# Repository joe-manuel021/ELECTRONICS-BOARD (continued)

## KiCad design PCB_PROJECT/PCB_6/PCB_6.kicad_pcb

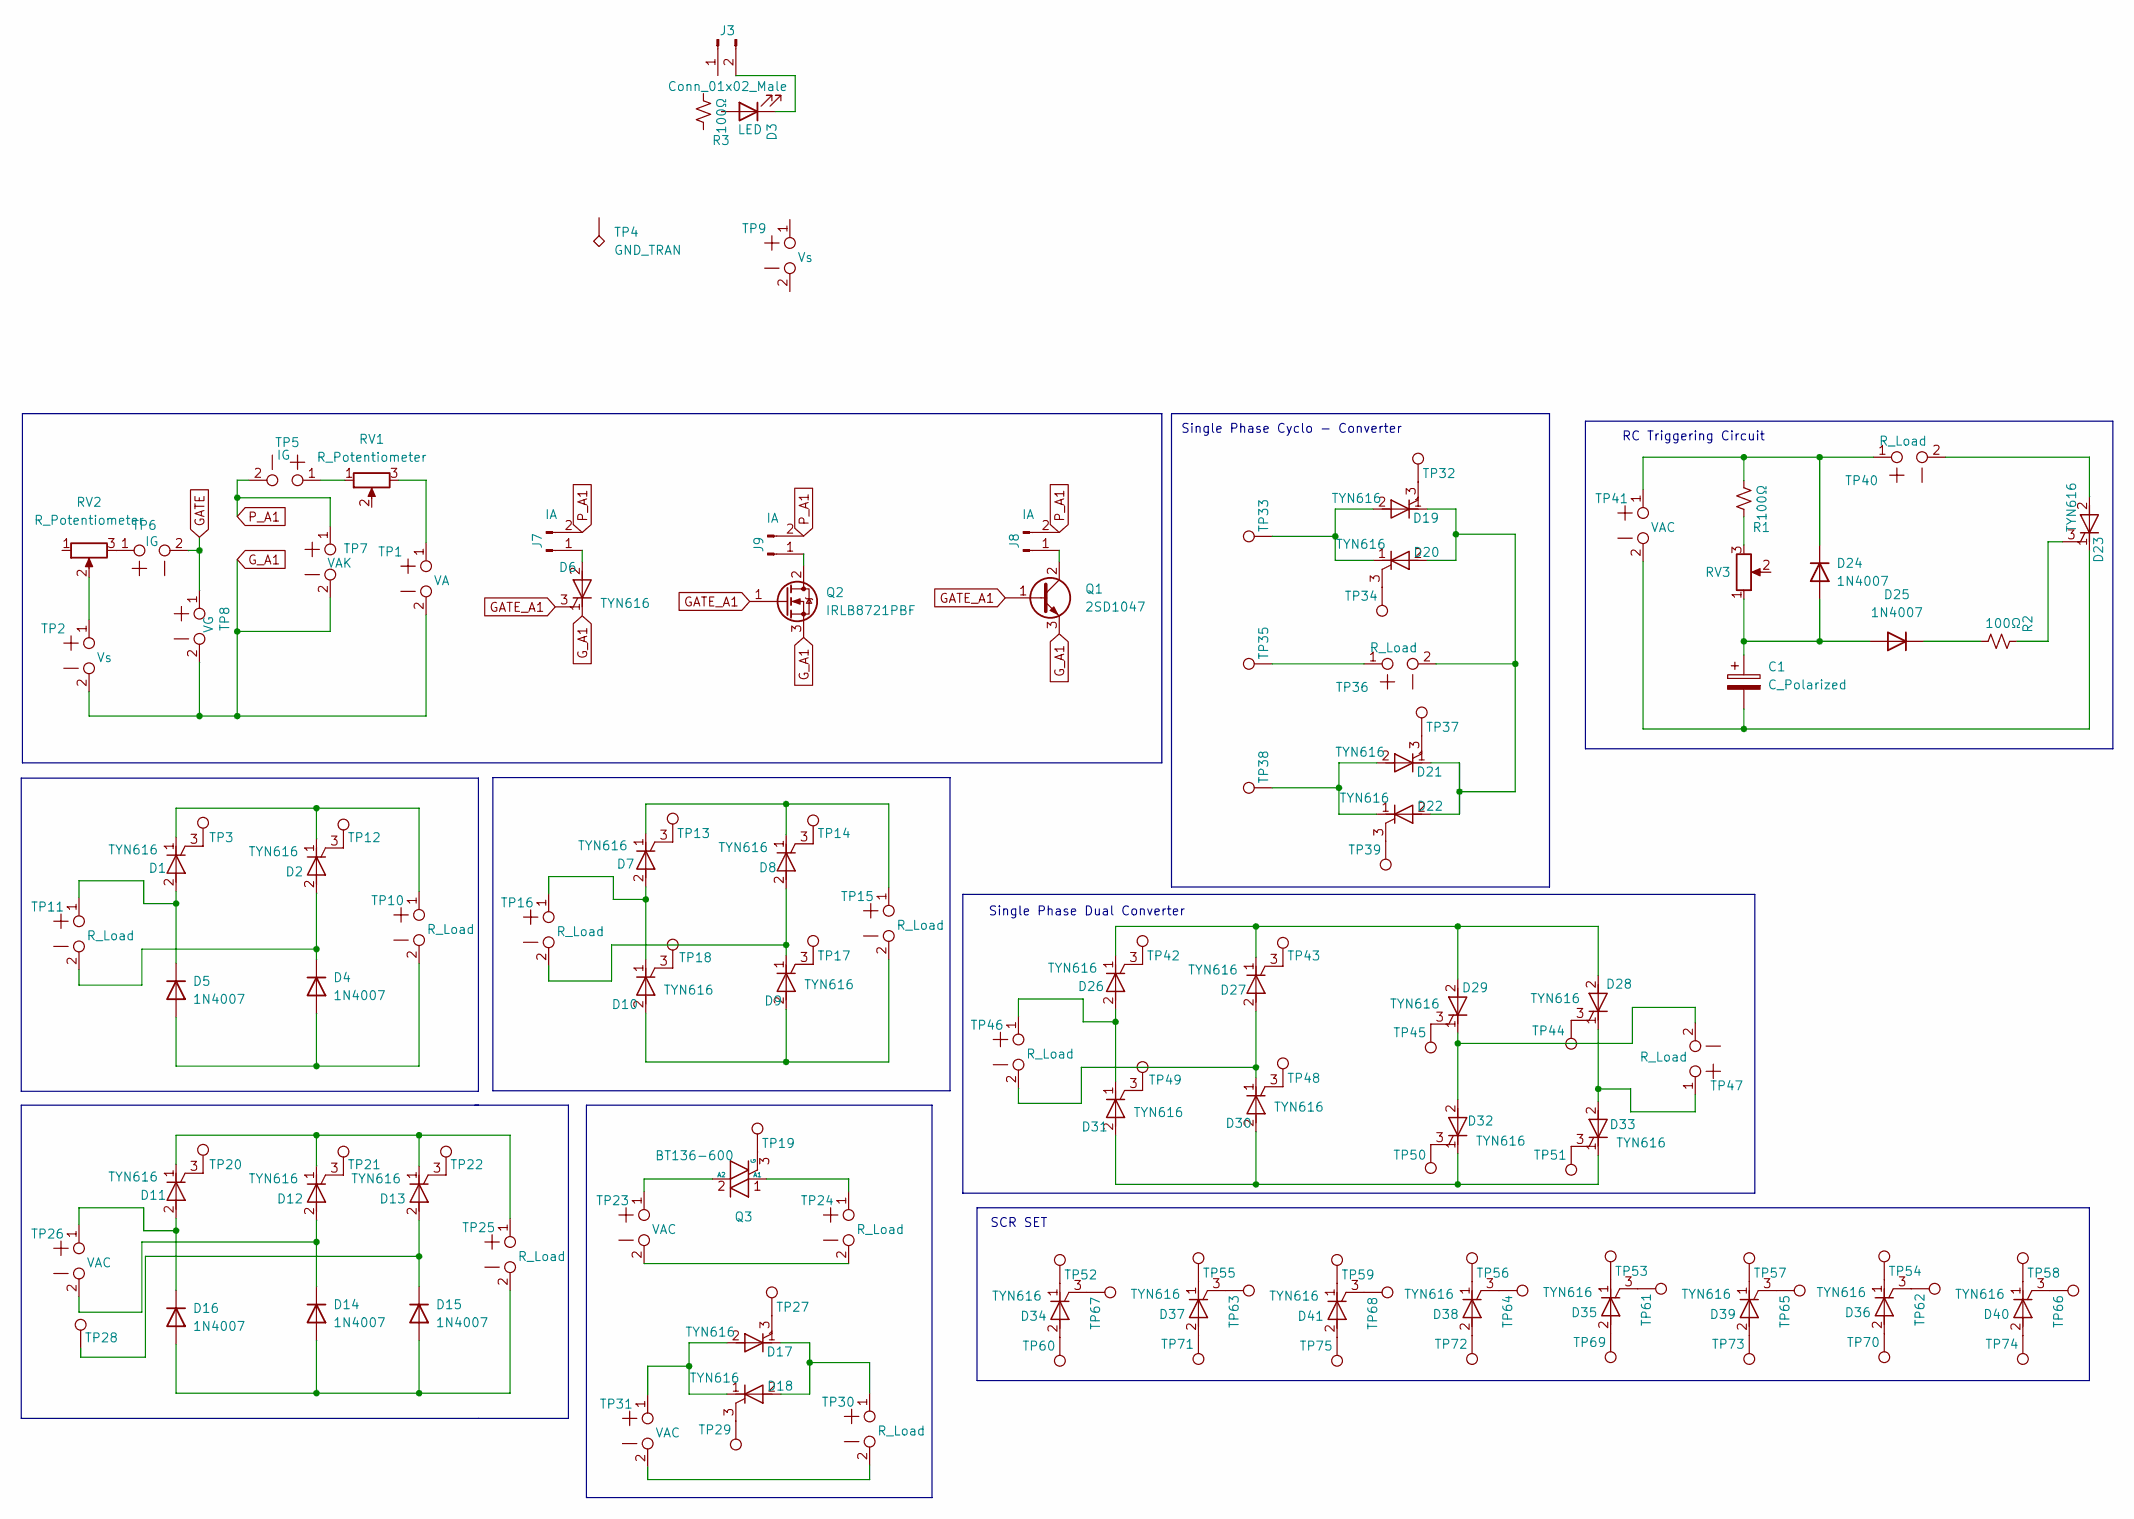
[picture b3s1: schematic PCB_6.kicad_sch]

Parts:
C1: C_Polarized
D1, D2, D6, D7, D8, D9, D10, D11, D12, D13, D17, D18, D19, D20, D21, D22, D23, D26, D27, D28, D29, D30, D31, D32, D33, D34, D35, D36, D37, D38, D39, D40, D41: TYN616; TO-220-3_Vertical
D3: LED; LED_D3.0mm
D4, D5, D14, D15, D16, D24, D25: 1N4007; D_DO-41_SOD81_P10.16mm_Horizontal
J3: Conn_01x02_Male; PinHeader_1x02_P2.54mm_Vertical
J7, J8, J9: IA; PinHeader_1x02_P2.54mm_Vertical
Q1: 2SD1047; TO-3PB-3_Vertical
Q2: IRLB8721PBF; TO-220-3_Vertical
Q3: BT136-600; TO-220-3_Vertical
R1, R2, R3: 100Ω; R_0805_2012Metric_Pad1.20x1.40mm_HandSolder
RV1, RV2, RV3: R_Potentiometer; Potentiometer_Piher_T-16L_Single_Vertical_Hole
TP1: VA; TestPoint_Pith10mm_Drill4mm
TP2, TP9: Vs; TestPoint_Pith10mm_Drill4mm
TP3, TP12, TP13, TP14, TP17, TP18, TP19, TP20, TP21, TP22, TP27, TP28, TP29, TP32, TP33, TP34, TP35, TP37, TP38, TP39, TP42, TP43, TP44, TP45, TP48, TP49, TP50, TP51, TP60, TP69, TP70, TP71, TP72, TP73, TP74, TP75: POWER_4MM
TP4: GND_TRAN; GND_4MM
TP5, TP6: IG; TestPoint_Pith10mm_Drill4mm
TP7: VAK; TestPoint_Pith10mm_Drill4mm
TP8: VG; TestPoint_Pith10mm_Drill4mm
TP10, TP11, TP15, TP16, TP24, TP25, TP30, TP36, TP40, TP46, TP47: R_Load; TestPoint_Pith10mm_Drill4mm
TP23, TP26, TP31, TP41: VAC; TestPoint_Pith10mm_Drill4mm
TP52, TP53, TP54, TP55, TP56, TP57, TP58, TP59: GND_4MM
TP61, TP62, TP63, TP64, TP65, TP66, TP67, TP68: POWER_4MM_GREEN

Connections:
GATE: TP6.2, TP8.1
GATE_A1: D6.3 (G), Q1.1 (B), Q2.1 (G)
G_A1: D6.1 (K), Q1.3 (E), Q2.3 (S), TP1.2, TP2.2, TP7.2, TP8.2
unnamed: C1.1, D24.2 (A), D25.2 (A), RV3.1
unnamed: C1.2, D23.1 (K), TP41.2
unnamed: D1.1 (K), D2.1 (K), TP10.1
unnamed: D1.2 (A), D5.1 (K), TP11.1
unnamed: D1.3 (G), TP3.1
unnamed: D2.2 (A), D4.1 (K), TP11.2
unnamed: D2.3 (G), TP12.1
unnamed: D3.1 (K), J3.2
unnamed: D4.2 (A), D5.2 (A), TP10.2
unnamed: D6.2 (A), J7.1
unnamed: D7.1 (K), D8.1 (K), TP15.1
unnamed: D7.3 (G), TP13.1
unnamed: D8.2 (A), D9.1 (K), TP16.2
unnamed: D8.3 (G), TP14.1
unnamed: D9.3 (G), TP17.1
unnamed: D7.2 (A), D10.1 (K), TP16.1
unnamed: D9.2 (A), D10.2 (A), TP15.2
unnamed: D10.3 (G), TP18.1
unnamed: D11.1 (K), D12.1 (K), D13.1 (K), TP25.1
unnamed: D11.2 (A), D16.1 (K), TP26.1
unnamed: D11.3 (G), TP20.1
unnamed: D12.2 (A), D14.1 (K), TP26.2
unnamed: D12.3 (G), TP21.1
unnamed: D13.2 (A), D15.1 (K), TP28.1
unnamed: D13.3 (G), TP22.1
unnamed: D14.2 (A), D15.2 (A), D16.2 (A), TP25.2
unnamed: D17.1 (K), D18.2 (A), TP30.1
unnamed: D17.2 (A), D18.1 (K), TP31.1
unnamed: D17.3 (G), TP27.1
unnamed: D18.3 (G), TP29.1
unnamed: D19.1 (K), D20.2 (A), D21.1 (K), D22.2 (A), TP36.2
unnamed: D19.2 (A), D20.1 (K), TP33.1
unnamed: D19.3 (G), TP32.1
unnamed: D20.3 (G), TP34.1
unnamed: D21.2 (A), D22.1 (K), TP38.1
unnamed: D21.3 (G), TP37.1
unnamed: D22.3 (G), TP39.1
unnamed: D23.2 (A), TP40.2
unnamed: D23.3 (G), R2.2
unnamed: D24.1 (K), R1.1, TP40.1, TP41.1
unnamed: D25.1 (K), R2.1
unnamed: D26.1 (K), D27.1 (K), D28.2 (A), D29.2 (A)
unnamed: D26.2 (A), D31.1 (K), TP46.1
unnamed: D26.3 (G), TP42.1
unnamed: D27.2 (A), D30.1 (K), TP46.2
unnamed: D27.3 (G), TP43.1
unnamed: D28.1 (K), D33.2 (A), TP47.1
unnamed: D28.3 (G), TP44.1
unnamed: D29.1 (K), D32.2 (A), TP47.2
unnamed: D29.3 (G), TP45.1
unnamed: D30.2 (A), D31.2 (A), D32.1 (K), D33.1 (K)
unnamed: D30.3 (G), TP48.1
unnamed: D31.3 (G), TP49.1
unnamed: D32.3 (G), TP50.1
unnamed: D33.3 (G), TP51.1
unnamed: D34.1 (K), TP52.1
unnamed: D34.2 (A), TP60.1
unnamed: D34.3 (G), TP67.1
unnamed: D35.1 (K), TP53.1
unnamed: D35.2 (A), TP69.1
unnamed: D35.3 (G), TP61.1
unnamed: D36.1 (K), TP54.1
unnamed: D36.2 (A), TP70.1
unnamed: D36.3 (G), TP62.1
unnamed: D37.1 (K), TP55.1
unnamed: D37.2 (A), TP71.1
unnamed: D37.3 (G), TP63.1
unnamed: D38.1 (K), TP56.1
unnamed: D38.2 (A), TP72.1
unnamed: D38.3 (G), TP64.1
unnamed: D39.1 (K), TP57.1
unnamed: D39.2 (A), TP73.1
unnamed: D39.3 (G), TP65.1
unnamed: D40.1 (K), TP58.1
unnamed: D40.2 (A), TP74.1
unnamed: D40.3 (G), TP66.1
unnamed: D41.1 (K), TP59.1
unnamed: D41.2 (A), TP75.1
unnamed: D41.3 (G), TP68.1
unnamed: J8.1, Q1.2 (C)
unnamed: J9.1, Q2.2 (D)
unnamed: Q3.1 (A1), TP24.1
unnamed: Q3.2 (A2), TP23.1
unnamed: Q3.3 (G), TP19.1
unnamed: R1.2, RV3.3
unnamed: RV1.1, TP5.1
unnamed: RV1.3, TP1.1
unnamed: RV2.2, TP2.1
unnamed: RV2.3, TP6.1
unnamed: TP23.2, TP24.2
unnamed: TP30.2, TP31.2
unnamed: TP35.1, TP36.1
P_A1: J7.2, J8.2, J9.2, TP5.2, TP7.1

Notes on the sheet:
SCR SET
RC Triggering Circuit
Single Phase Dual Converter
Single Phase Cyclo - Converter

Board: 2 copper layers, 129 parts (0 on the bottom side), 96 nets, no tracks yet.

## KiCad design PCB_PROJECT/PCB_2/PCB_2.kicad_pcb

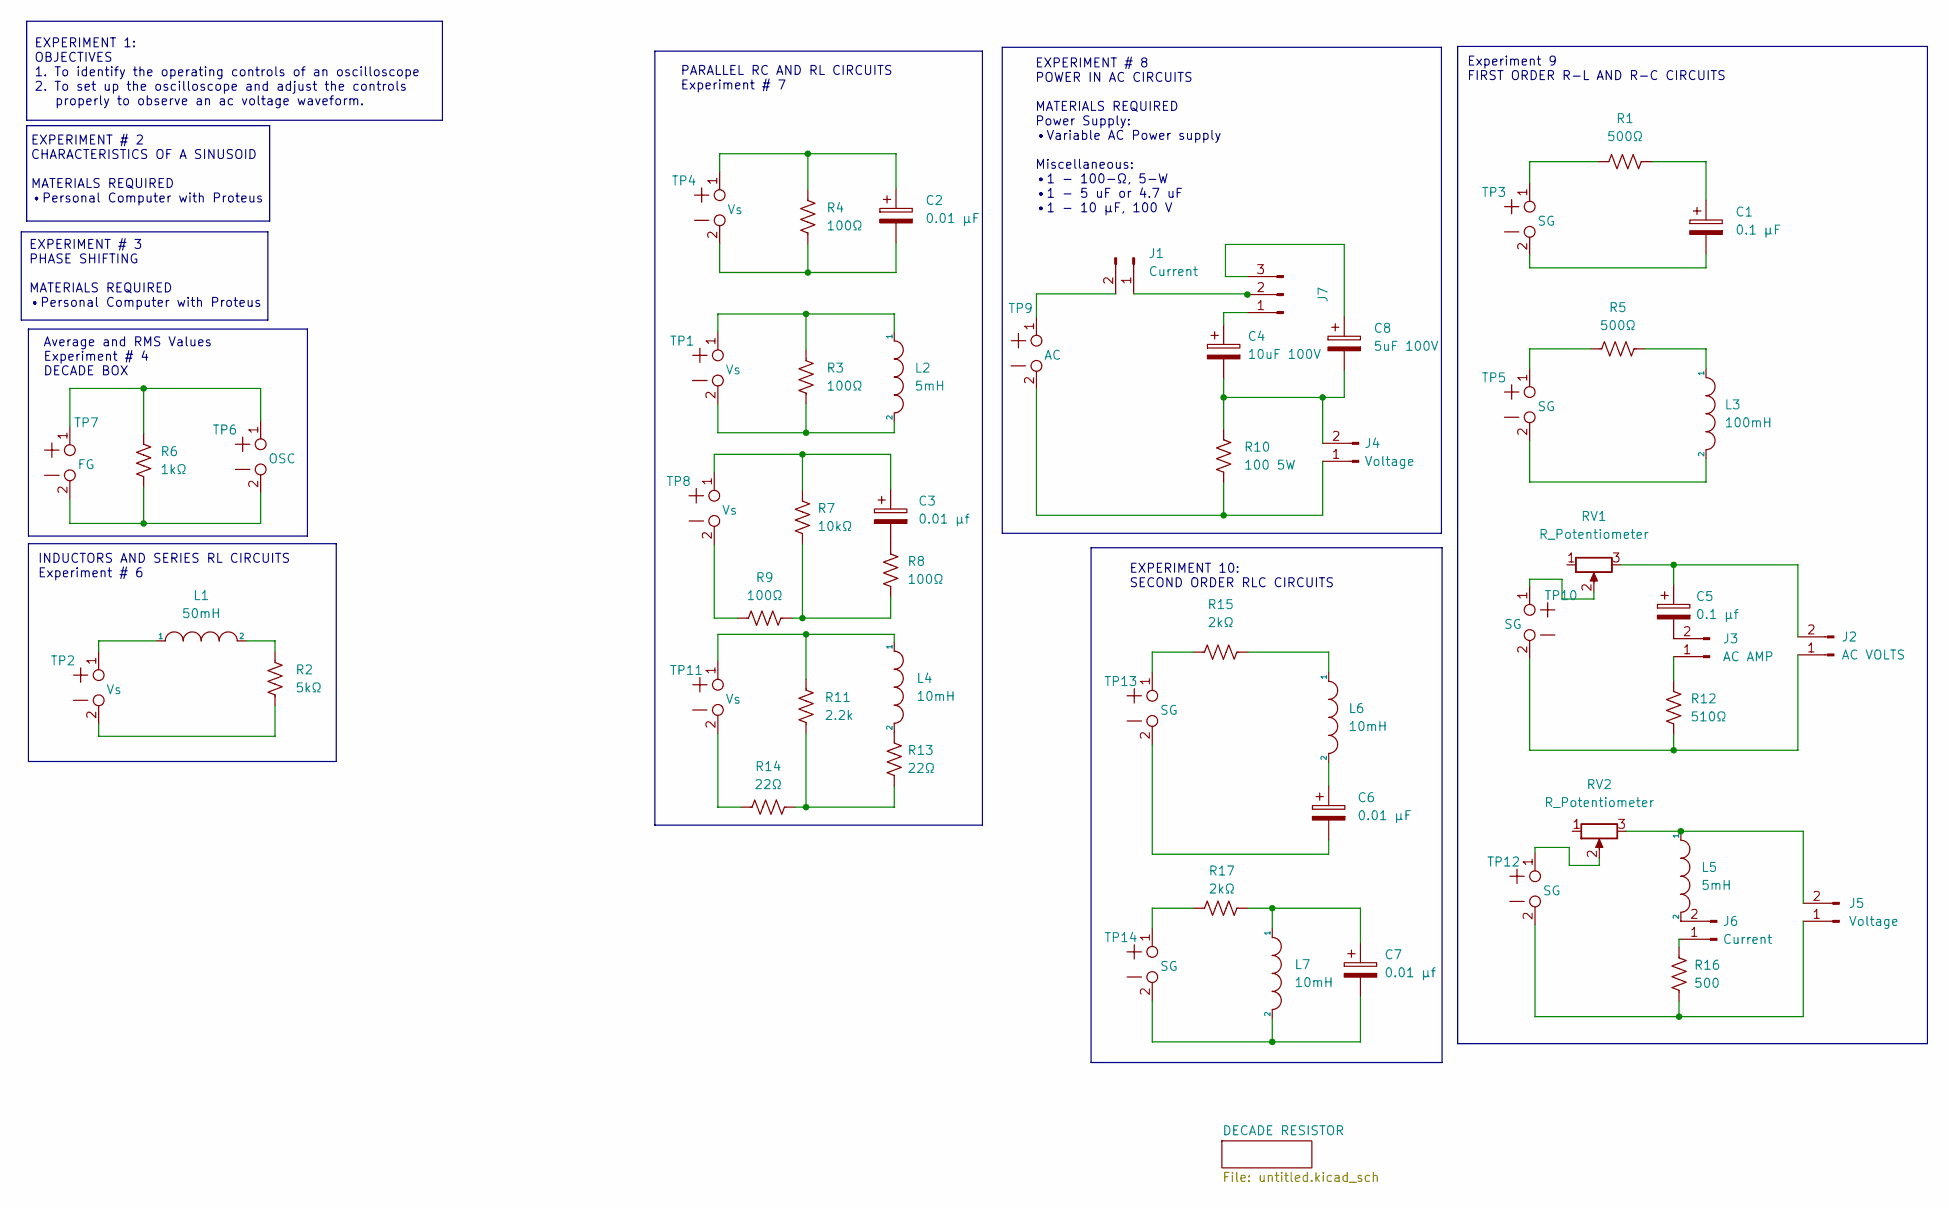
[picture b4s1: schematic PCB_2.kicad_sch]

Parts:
C1: 0.1 μF; 0.022uF_Capacitor
C2: 0.01 μF; C_Rect_L10.0mm_W4.0mm_P7.50mm_MKS4
C3: 0.01 μf; C_Rect_L10.0mm_W4.0mm_P7.50mm_MKS4
C4: 10uF 100V; CP_Elec_6.3x7.7
C5: 0.1 μf; 0.022uF_Capacitor
C6: 0.01 μF; 0.022uF_Capacitor
C7: 0.01 μf; 0.022uF_Capacitor
C8: 5uF 100V; CP_Elec_6.3x5.4
J1, J6: Current; PinHeader_1x02_P2.54mm_Vertical
J2: AC VOLTS; PinHeader_1x02_P2.54mm_Vertical
J3: AC AMP; PinHeader_1x02_P2.54mm_Vertical
J4, J5: Voltage; PinHeader_1x02_P2.54mm_Vertical
J7: Conn_01x03_Male; PinHeader_1x03_P2.54mm_Vertical
L1: 50mH; L_Axial_L12.0mm_D5.0mm_P15.24mm_Horizontal_Fastron_MISC
L2, L5: 5mH; L_Axial_L12.0mm_D5.0mm_P15.24mm_Horizontal_Fastron_MISC
L3: 100mH; L_Axial_L12.0mm_D5.0mm_P15.24mm_Horizontal_Fastron_MISC
L4, L6, L7: 10mH; L_Axial_L12.0mm_D5.0mm_P15.24mm_Horizontal_Fastron_MISC
R1, R5: 500Ω; R_Axial_DIN0309_L9.0mm_D3.2mm_P12.70mm_Horizontal
R2: 5kΩ; R_Axial_DIN0309_L9.0mm_D3.2mm_P12.70mm_Horizontal
R3, R4, R8, R9: 100Ω; R_Axial_DIN0309_L9.0mm_D3.2mm_P12.70mm_Horizontal
R6: 1kΩ; R_Axial_DIN0309_L9.0mm_D3.2mm_P12.70mm_Horizontal
R7: 10kΩ; R_Axial_DIN0309_L9.0mm_D3.2mm_P12.70mm_Horizontal
R10: 100 5W; R_Axial_DIN0922_L20.0mm_D9.0mm_P30.48mm_Horizontal
R11: 2.2k; R_Axial_DIN0309_L9.0mm_D3.2mm_P12.70mm_Horizontal
R12: 510Ω; R_Axial_DIN0309_L9.0mm_D3.2mm_P12.70mm_Horizontal
R13, R14: 22Ω; R_Axial_DIN0309_L9.0mm_D3.2mm_P12.70mm_Horizontal
R15, R17: 2kΩ; R_Axial_DIN0309_L9.0mm_D3.2mm_P12.70mm_Horizontal
R16: 500; R_Axial_DIN0309_L9.0mm_D3.2mm_P12.70mm_Horizontal
RV1, RV2: R_Potentiometer; Potentiometer_Alps_RK09Y11_Single_Horizontal
TP1, TP2, TP4, TP8, TP11: Vs; TestPoint_Pith10mm_Drill4mm
TP3, TP5, TP10, TP12, TP13, TP14: SG; TestPoint_Pith10mm_Drill4mm
TP6: OSC; TestPoint_Pith10mm_Drill4mm
TP7: FG; TestPoint_Pith10mm_Drill4mm
TP9: AC; TestPoint_Pith10mm_Drill4mm

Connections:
unnamed: C1.1, R1.2
unnamed: C1.2, TP3.2
unnamed: C2.1, R4.1, TP4.1
unnamed: C2.2, R4.2, TP4.2
unnamed: C3.1, R7.1, TP8.1
unnamed: C3.2, R8.1
unnamed: C4.1, J7.1
unnamed: C4.2, C8.2, J4.2, R10.1
unnamed: C5.1, J2.2, RV1.3
unnamed: C5.2, J3.2
unnamed: C6.1, L6.2
unnamed: C6.2, TP13.2
unnamed: C7.1, L7.1, R17.1
unnamed: C7.2, L7.2, TP14.2
unnamed: C8.1, J7.3
unnamed: J1.1, J7.2
unnamed: J1.2, TP9.1
unnamed: J2.1, R12.1, TP10.2
unnamed: J3.1, R12.2
unnamed: J4.1, R10.2, TP9.2
unnamed: J5.1, R16.1, TP12.2
unnamed: J5.2, L5.1, RV2.3
unnamed: J6.1, R16.2
unnamed: J6.2, L5.2
unnamed: L1.1, TP2.1
unnamed: L1.2, R2.1
unnamed: L2.1, R3.1, TP1.1
unnamed: L2.2, R3.2, TP1.2
unnamed: L3.1, R5.2
unnamed: L3.2, TP5.2
unnamed: L4.1, R11.1, TP11.1
unnamed: L4.2, R13.1
unnamed: L6.1, R15.1
unnamed: R1.1, TP3.1
unnamed: R2.2, TP2.2
unnamed: R5.1, TP5.1
unnamed: R6.1, TP6.1, TP7.1
unnamed: R6.2, TP6.2, TP7.2
unnamed: R7.2, R8.2, R9.2
unnamed: R9.1, TP8.2
unnamed: R11.2, R13.2, R14.2
unnamed: R14.1, TP11.2
unnamed: R15.2, TP13.1
unnamed: R17.2, TP14.1
unnamed: RV2.2, TP12.1
unnamed: RV1.2, TP10.1

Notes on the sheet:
EXPERIMENT 10: SECOND ORDER RLC CIRCUITS
INDUCTORS AND SERIES RL CIRCUITS Experiment # 6
EXPERIMENT # 2 CHARACTERISTICS OF A SINUSOID MATERIALS REQUIRED •Personal Computer with Proteus
EXPERIMENT # 3 PHASE SHIFTING MATERIALS REQUIRED •Personal Computer with Proteus
EXPERIMENT # 8 POWER IN AC CIRCUITS MATERIALS REQUIRED Power Supply: •Variable AC Power supply Miscellaneous: •1 - 100-Ω, 5-W •1 - 5 uF or 4.7 uF •1 - 10 μF, 100 V
Average and RMS Values Experiment # 4 DECADE BOX
Experiment 9 FIRST ORDER R-L AND R-C CIRCUITS
EXPERIMENT 1: OBJECTIVES 1. To identify the operating controls of an oscilloscope 2. To set up the oscilloscope and adjust the controls properly to observe an ac voltage waveform.
PARALLEL RC AND RL CIRCUITS Experiment # 7

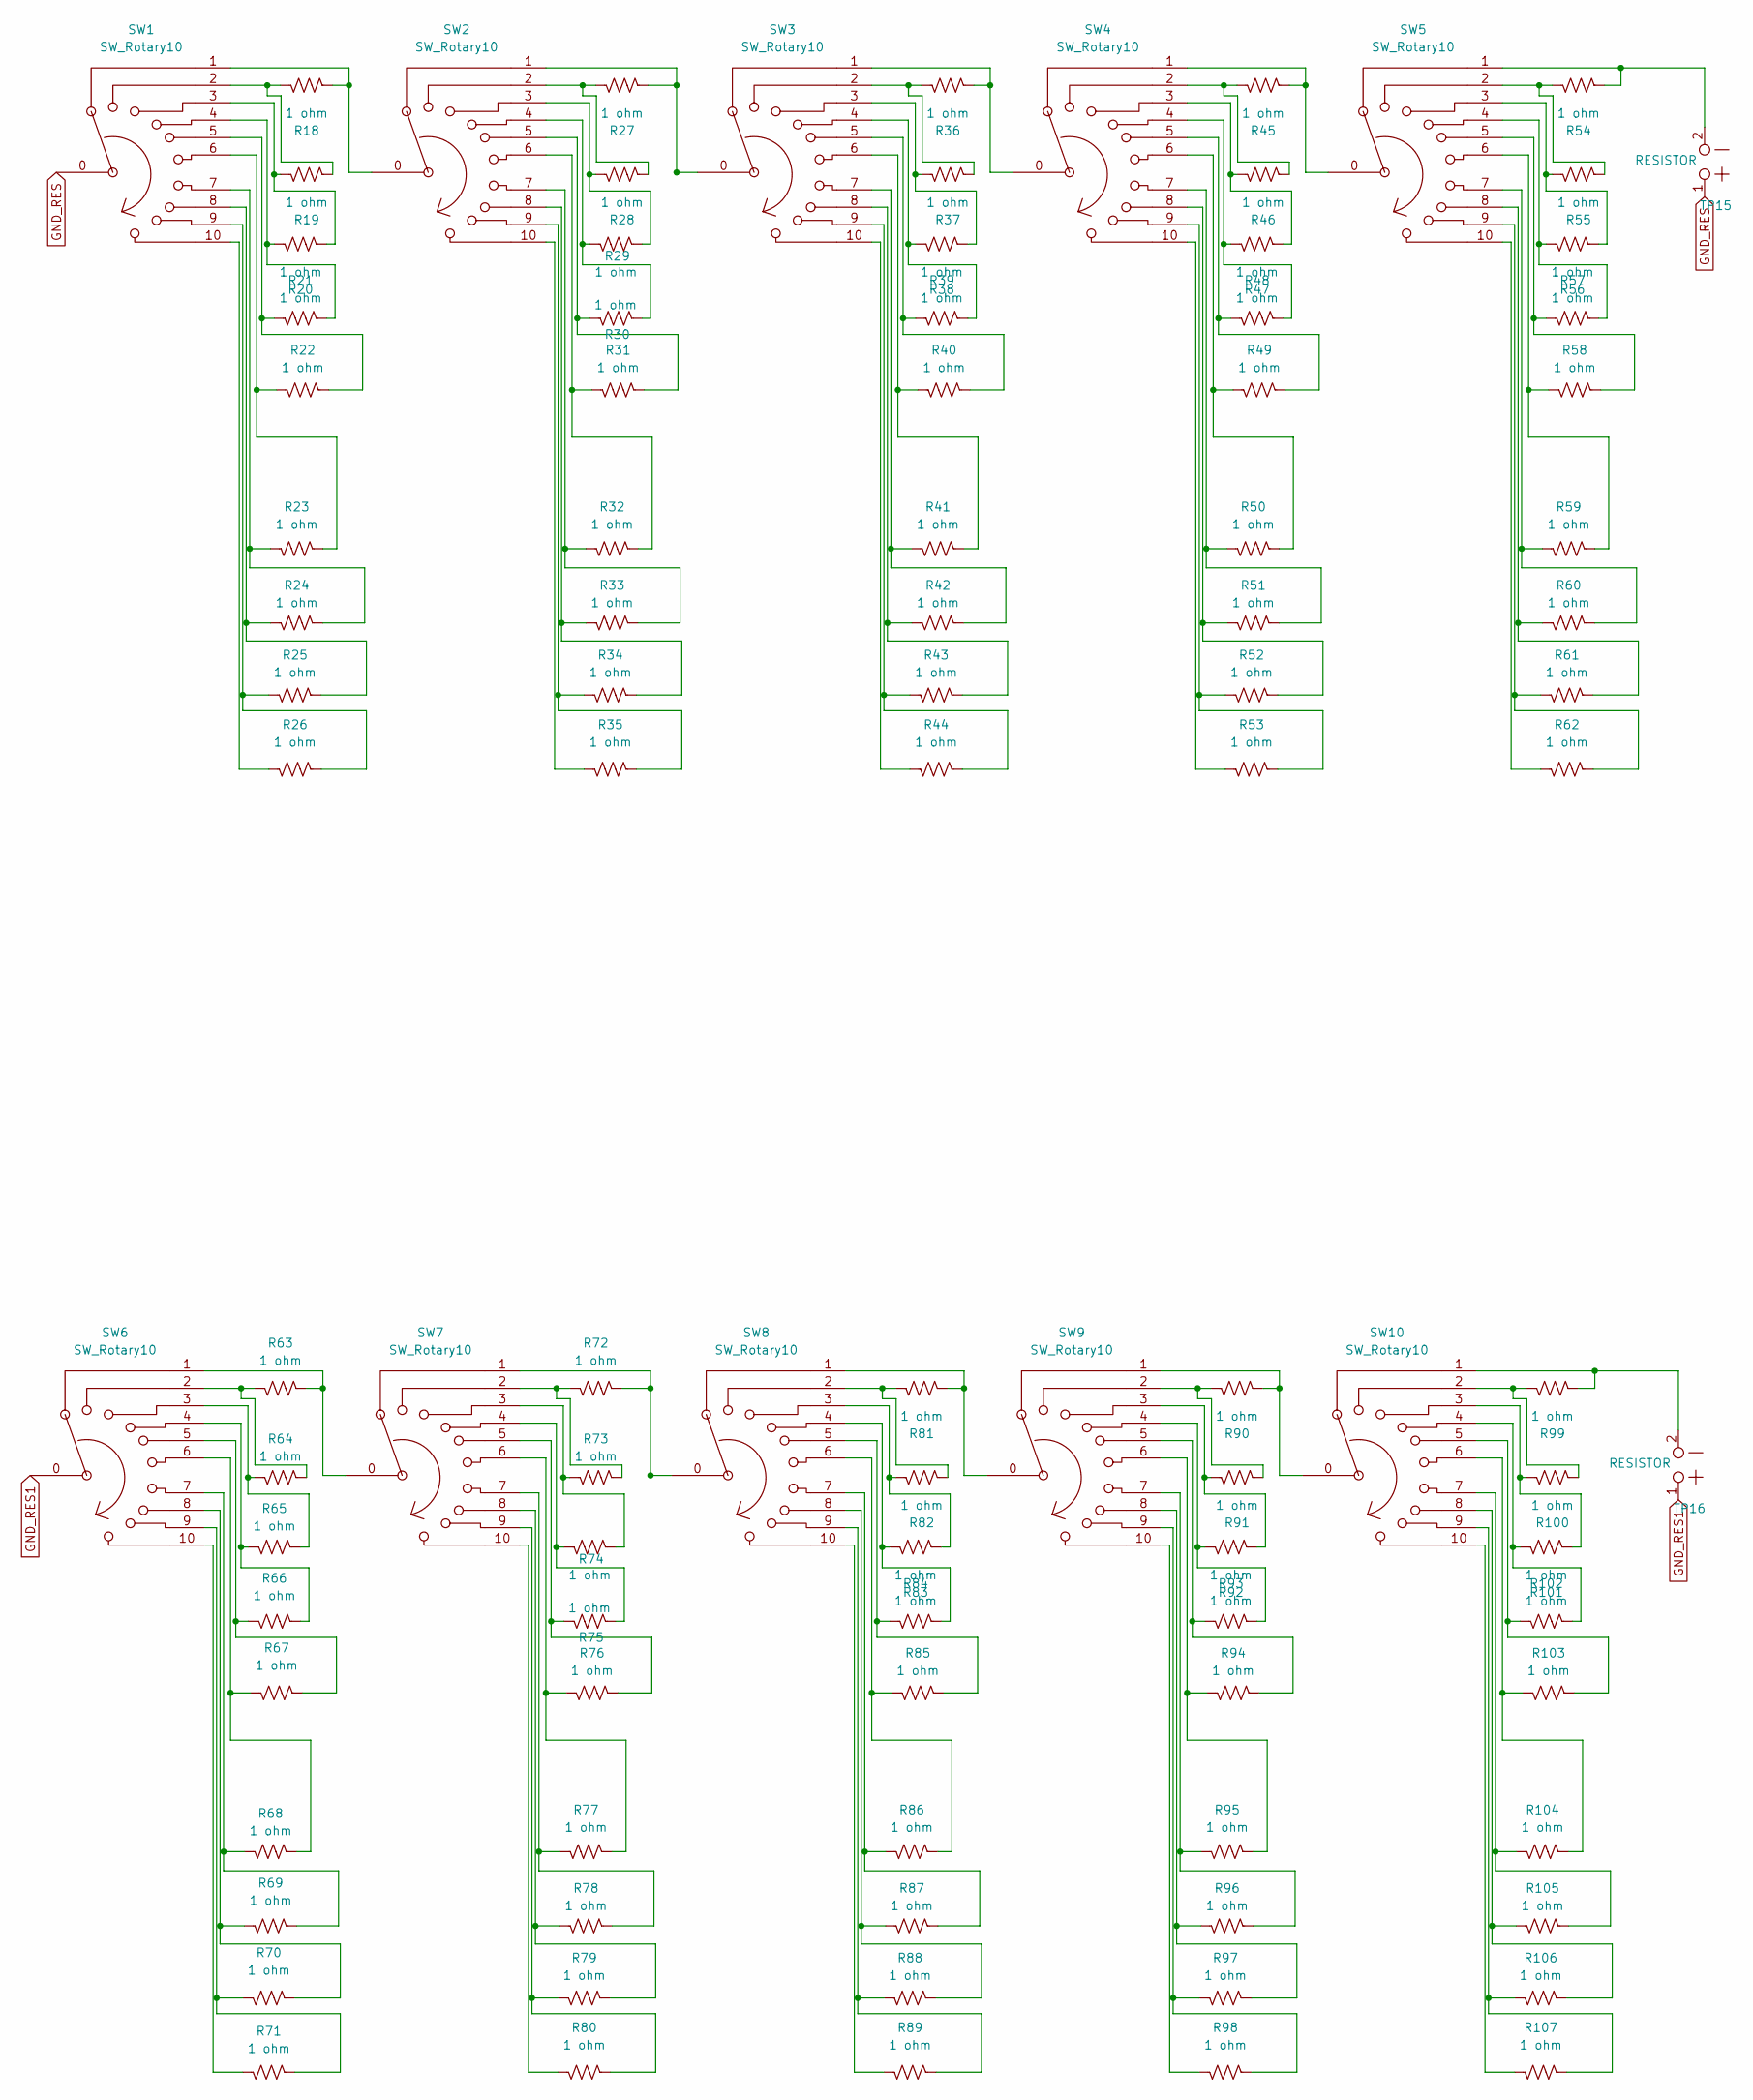
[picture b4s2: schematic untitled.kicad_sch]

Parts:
R18, R19, R20, R21, R22, R23, R24, R25, R26, R27, R28, R29, R30, R31, R32, R33, R34, R35, R36, R37, R38, R39, R40, R41, R42, R43, R44, R45, R46, R47, R48, R49, R50, R51, R52, R53, R54, R55, R56, R57, R58, R59, R60, R61, R62, R63, R64, R65, R66, R67, R68, R69, R70, R71, R72, R73, R74, R75, R76, R77, R78, R79, R80, R81, R82, R83, R84, R85, R86, R87, R88, R89, R90, R91, R92, R93, R94, R95, R96, R97, R98, R99, R100, R101, R102, R103, R104, R105, R106, R107: 1 ohm; R_Axial_DIN0207_L6.3mm_D2.5mm_P10.16mm_Horizontal
SW1, SW2, SW3, SW4, SW5, SW6, SW7, SW8, SW9, SW10: SW_Rotary10; rotary_10
TP15, TP16: RESISTOR; TestPoint_Pith10mm_Drill4mm

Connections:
GND_RES: SW1.0, TP15.1
GND_RES1: SW6.0, TP16.1
unnamed: R18.1, R19.2, SW1.2
unnamed: R18.2, SW1.1, SW2.0
unnamed: R19.1, R20.2, SW1.3
unnamed: R20.1, R21.2, SW1.4
unnamed: R21.1, R22.2, SW1.5
unnamed: R22.1, R23.2, SW1.6
unnamed: R23.1, R24.2, SW1.7
unnamed: R24.1, R25.2, SW1.8
unnamed: R25.1, R26.2, SW1.9
unnamed: R26.1, SW1.10
unnamed: R27.1, R28.2, SW2.2
unnamed: R27.2, SW2.1, SW3.0
unnamed: R28.1, R29.2, SW2.3
unnamed: R29.1, R30.2, SW2.4
unnamed: R30.1, R31.2, SW2.5
unnamed: R31.1, R32.2, SW2.6
unnamed: R32.1, R33.2, SW2.7
unnamed: R33.1, R34.2, SW2.8
unnamed: R34.1, R35.2, SW2.9
unnamed: R35.1, SW2.10
unnamed: R36.1, R37.2, SW3.2
unnamed: R36.2, SW3.1, SW4.0
unnamed: R37.1, R38.2, SW3.3
unnamed: R38.1, R39.2, SW3.4
unnamed: R39.1, R40.2, SW3.5
unnamed: R40.1, R41.2, SW3.6
unnamed: R41.1, R42.2, SW3.7
unnamed: R42.1, R43.2, SW3.8
unnamed: R43.1, R44.2, SW3.9
unnamed: R44.1, SW3.10
unnamed: R45.1, R46.2, SW4.2
unnamed: R45.2, SW4.1, SW5.0
unnamed: R46.1, R47.2, SW4.3
unnamed: R47.1, R48.2, SW4.4
unnamed: R48.1, R49.2, SW4.5
unnamed: R49.1, R50.2, SW4.6
unnamed: R50.1, R51.2, SW4.7
unnamed: R51.1, R52.2, SW4.8
unnamed: R52.1, R53.2, SW4.9
unnamed: R53.1, SW4.10
unnamed: R54.1, R55.2, SW5.2
unnamed: R54.2, SW5.1, TP15.2
unnamed: R55.1, R56.2, SW5.3
unnamed: R56.1, R57.2, SW5.4
unnamed: R57.1, R58.2, SW5.5
unnamed: R58.1, R59.2, SW5.6
unnamed: R59.1, R60.2, SW5.7
unnamed: R60.1, R61.2, SW5.8
unnamed: R61.1, R62.2, SW5.9
unnamed: R62.1, SW5.10
unnamed: R63.1, R64.2, SW6.2
unnamed: R63.2, SW6.1, SW7.0
unnamed: R64.1, R65.2, SW6.3
unnamed: R65.1, R66.2, SW6.4
unnamed: R66.1, R67.2, SW6.5
unnamed: R67.1, R68.2, SW6.6
unnamed: R68.1, R69.2, SW6.7
unnamed: R69.1, R70.2, SW6.8
unnamed: R70.1, R71.2, SW6.9
unnamed: R71.1, SW6.10
unnamed: R72.1, R73.2, SW7.2
unnamed: R72.2, SW7.1, SW8.0
unnamed: R73.1, R74.2, SW7.3
unnamed: R74.1, R75.2, SW7.4
unnamed: R75.1, R76.2, SW7.5
unnamed: R76.1, R77.2, SW7.6
unnamed: R77.1, R78.2, SW7.7
unnamed: R78.1, R79.2, SW7.8
unnamed: R79.1, R80.2, SW7.9
unnamed: R80.1, SW7.10
unnamed: R81.1, R82.2, SW8.2
unnamed: R81.2, SW8.1, SW9.0
unnamed: R82.1, R83.2, SW8.3
unnamed: R83.1, R84.2, SW8.4
unnamed: R84.1, R85.2, SW8.5
unnamed: R85.1, R86.2, SW8.6
unnamed: R86.1, R87.2, SW8.7
unnamed: R87.1, R88.2, SW8.8
unnamed: R88.1, R89.2, SW8.9
unnamed: R89.1, SW8.10
unnamed: R90.1, R91.2, SW9.2
unnamed: R90.2, SW9.1, SW10.0
unnamed: R91.1, R92.2, SW9.3
unnamed: R92.1, R93.2, SW9.4
unnamed: R93.1, R94.2, SW9.5
unnamed: R94.1, R95.2, SW9.6
unnamed: R95.1, R96.2, SW9.7
unnamed: R96.1, R97.2, SW9.8
unnamed: R97.1, R98.2, SW9.9
unnamed: R98.1, SW9.10
unnamed: R99.2, SW10.1, TP16.2
unnamed: R100.1, R101.2, SW10.3
unnamed: R99.1, R100.2, SW10.2
unnamed: R101.1, R102.2, SW10.4
unnamed: R102.1, R103.2, SW10.5
unnamed: R103.1, R104.2, SW10.6
unnamed: R104.1, R105.2, SW10.7
unnamed: R105.1, R106.2, SW10.8
unnamed: R106.1, R107.2, SW10.9
unnamed: R107.1, SW10.10

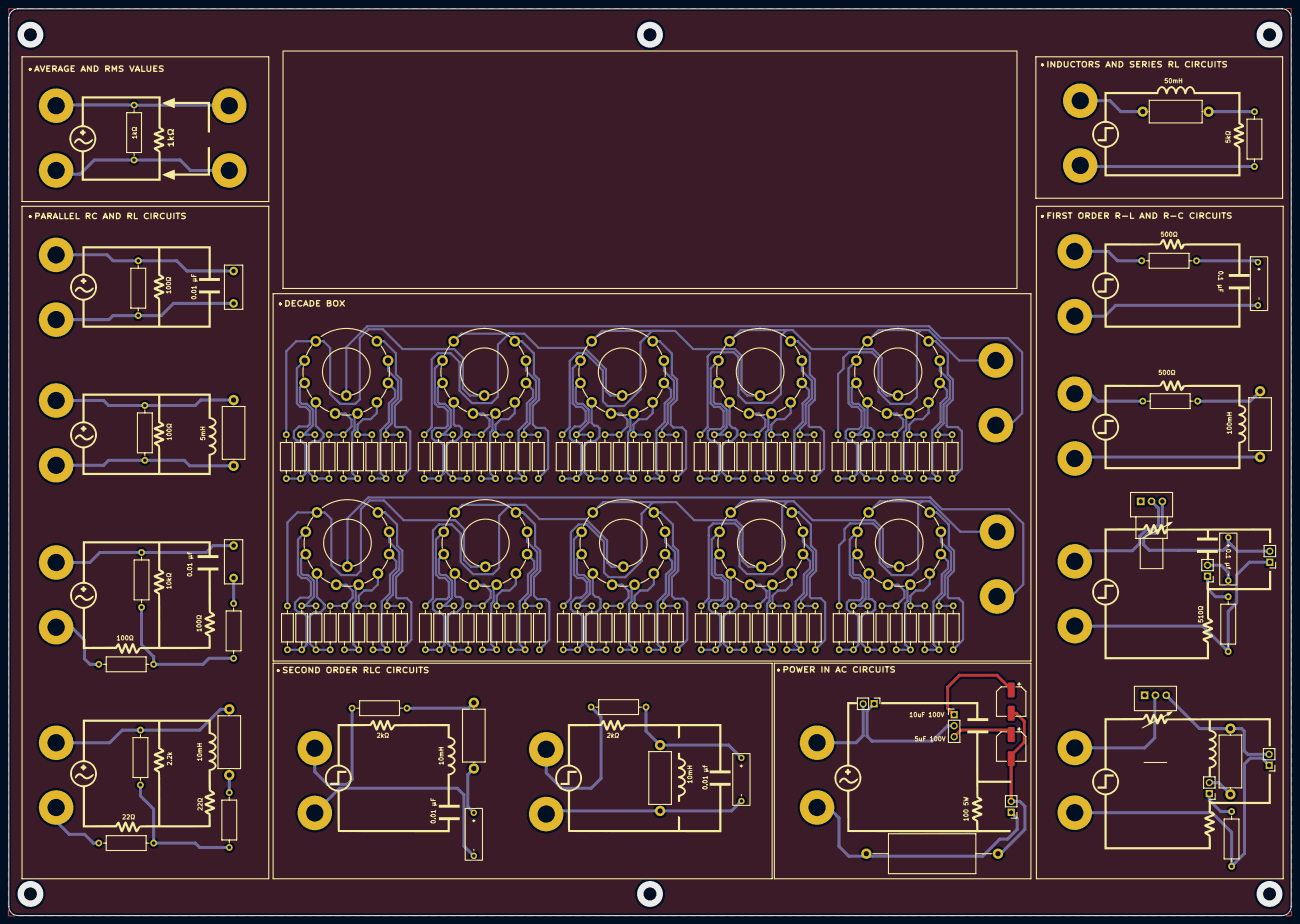
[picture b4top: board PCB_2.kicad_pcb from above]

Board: 2 copper layers, 297.0 x 210.0 mm, 158 parts (0 on the bottom side), 148 nets.

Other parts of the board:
 : LOGO; PCB2_ALL
